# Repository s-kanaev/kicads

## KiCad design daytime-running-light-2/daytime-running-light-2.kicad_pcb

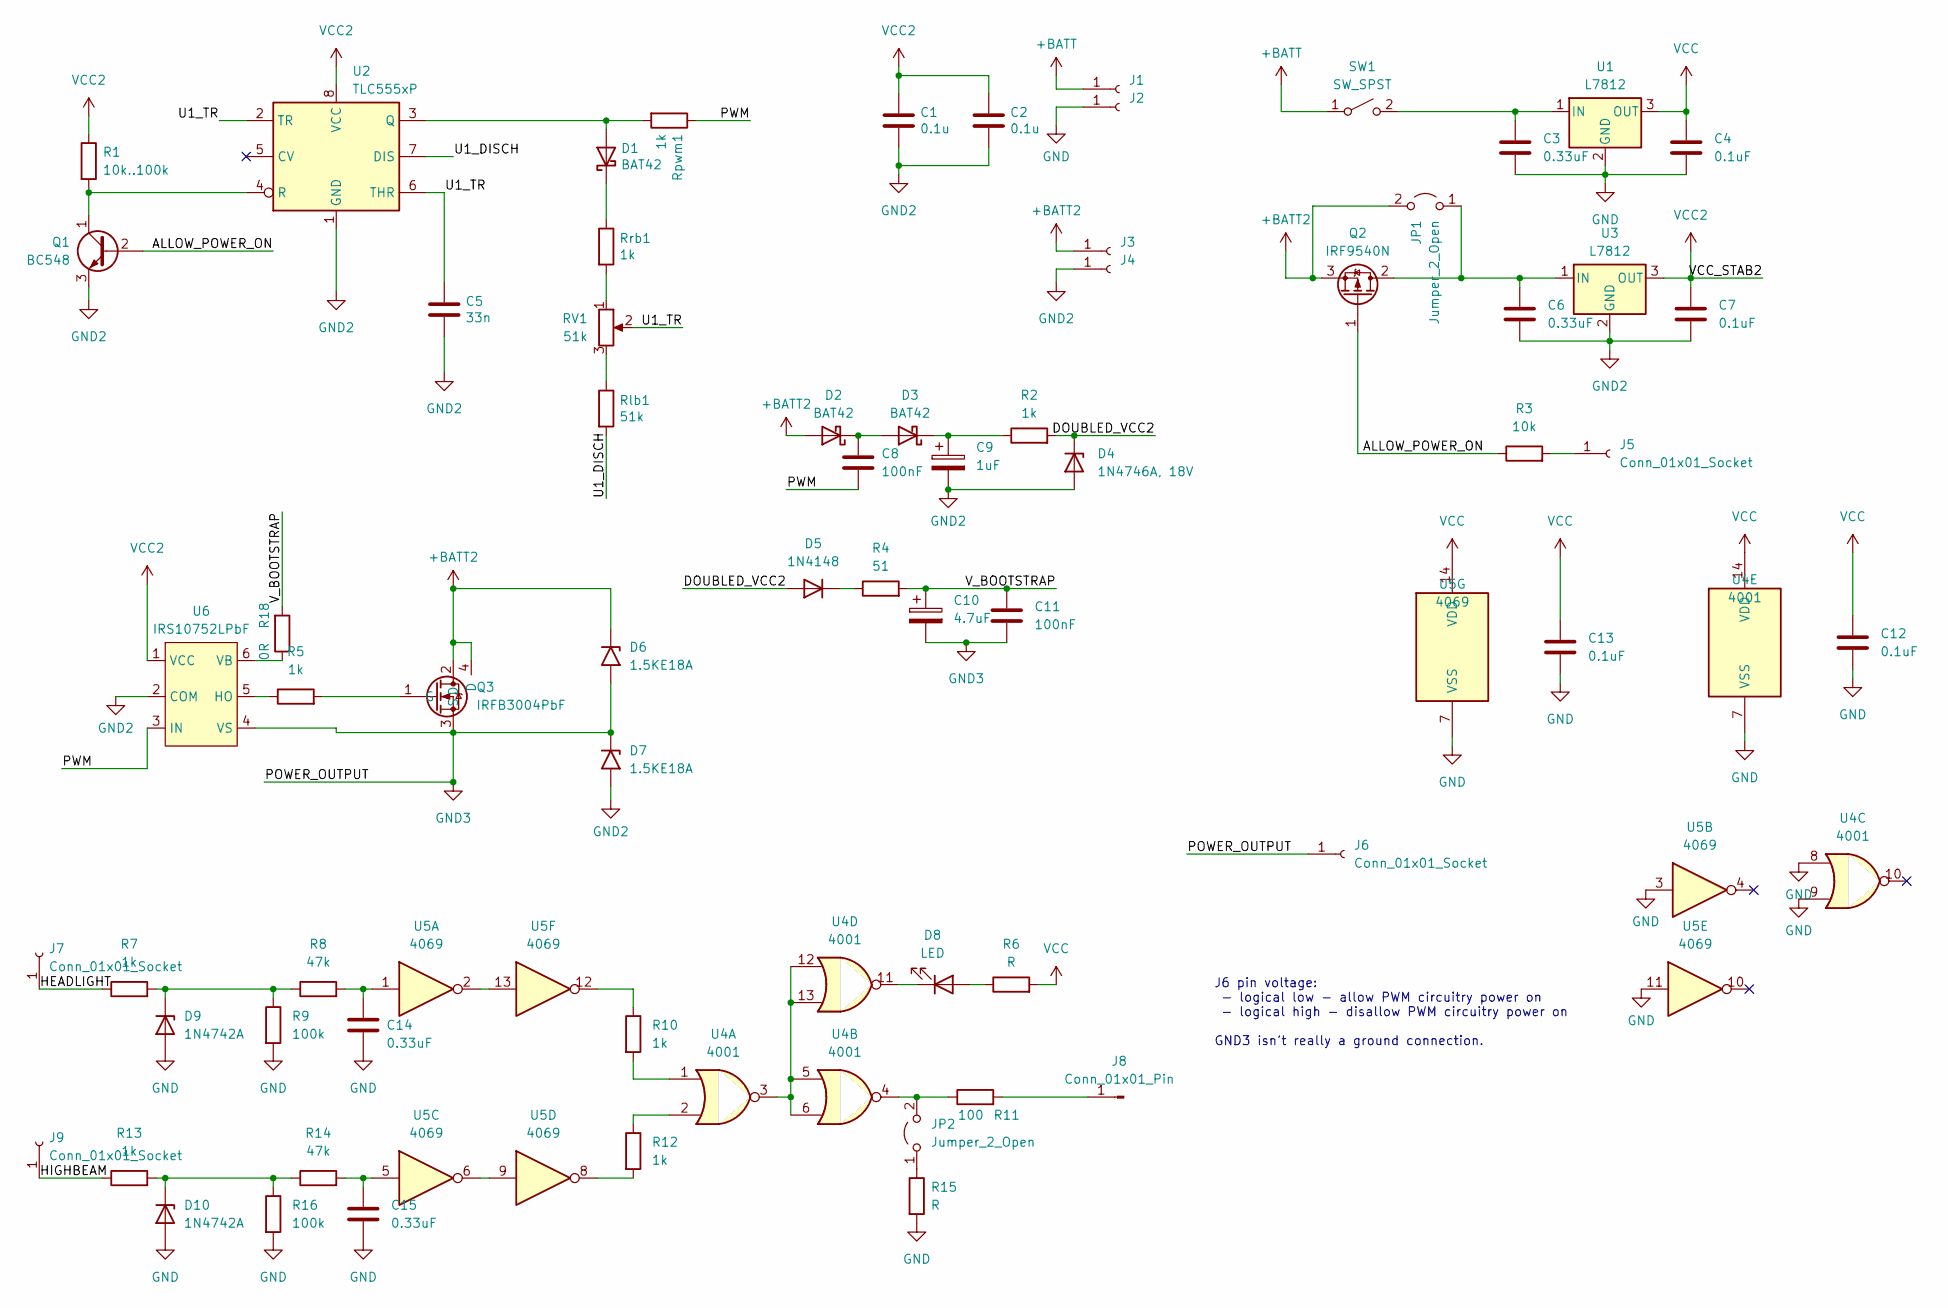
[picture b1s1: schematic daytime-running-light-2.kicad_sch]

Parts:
C1, C2: 0.1u; C_Disc_D6.0mm_W2.5mm_P5.00mm
C3, C6, C14, C15: 0.33uF; C_Disc_D6.0mm_W2.5mm_P5.00mm
C4, C7, C12, C13: 0.1uF; C_Disc_D6.0mm_W2.5mm_P5.00mm
C5: 33n; C_Disc_D6.0mm_W2.5mm_P5.00mm
C8, C11: 100nF; C_Disc_D6.0mm_W2.5mm_P5.00mm
C9: 1uF; CP_Radial_D5.0mm_P2.00mm
C10: 4.7uF; CP_Radial_D5.0mm_P2.00mm
D1: BAT42; D_DO-35_SOD27_P7.62mm_Horizontal
D2: BAT42; D_DO-35_SOD27_P5.08mm_Vertical_KathodeUp
D3: BAT42; D_DO-35_SOD27_P5.08mm_Vertical_AnodeUp
D4: 1N4746A, 18V; D_DO-41_SOD81_P3.81mm_Vertical_KathodeUp
D5: 1N4148; D_DO-35_SOD27_P7.62mm_Horizontal
D6, D7: 1.5KE18A; D_DO-201AE_P15.24mm_Horizontal
D8: LED; LED_D5.0mm
D9: 1N4742A; D_DO-41_SOD81_P3.81mm_Vertical_KathodeUp
D10: 1N4742A; D_DO-41_SOD81_P10.16mm_Horizontal
J1, J3, J6: Conn_01x01_Socket; SolderWire-2.5sqmm_1x01_D2.4mm_OD3.6mm
J2, J4: Conn_01x01_Socket; SolderWire-1.5sqmm_1x01_D1.7mm_OD3.9mm
J5, J7, J9: Conn_01x01_Socket; SolderWire-1.5sqmm_1x01_D1.7mm_OD3mm
J8: Conn_01x01_Pin; SolderWire-1.5sqmm_1x01_D1.7mm_OD3mm
JP1, JP2: Jumper_2_Open; SolderWire-0.75sqmm_1x02_P4.8mm_D1.25mm_OD2.3mm
Q1: BC548; TO-92_HandSolder2
Q2: IRF9540N; TO-220-3_Vertical-mod
Q3: IRFB3004PbF; TO-263-2
R1: 10k..100k; R_Axial_DIN0207_L6.3mm_D2.5mm_P7.62mm_Horizontal
R2, R7, R10, R12, R13: 1k; R_Axial_DIN0207_L6.3mm_D2.5mm_P2.54mm_Vertical
R3: 10k; R_Axial_DIN0207_L6.3mm_D2.5mm_P2.54mm_Vertical
R4: 51; R_Axial_DIN0207_L6.3mm_D2.5mm_P2.54mm_Vertical
R5: 1k; R_Axial_DIN0207_L6.3mm_D2.5mm_P7.62mm_Horizontal
R6, R15: R; R_Axial_DIN0207_L6.3mm_D2.5mm_P2.54mm_Vertical
R8, R14: 47k; R_Axial_DIN0207_L6.3mm_D2.5mm_P2.54mm_Vertical
R9, R16: 100k; R_Axial_DIN0207_L6.3mm_D2.5mm_P2.54mm_Vertical
R11: 100; R_Axial_DIN0207_L6.3mm_D2.5mm_P7.62mm_Horizontal
R18: 0R; R_Axial_DIN0207_L6.3mm_D2.5mm_P7.62mm_Horizontal
RV1: 51k; Potentiometer_Bourns_3296W_Vertical
Rlb1: 51k; R_Axial_DIN0207_L6.3mm_D2.5mm_P2.54mm_Vertical
Rpwm1: 1k; R_Axial_DIN0207_L6.3mm_D2.5mm_P5.08mm_Vertical
Rrb1: 1k; R_Axial_DIN0207_L6.3mm_D2.5mm_P7.62mm_Horizontal
SW1: SW_SPST; SolderWire-1.5sqmm_1x02_P6mm_D1.7mm_OD3mm
U1: L7812; TO-220-3_Vertical-mod
U2: TLC555xP; SOIC-8_3.9x4.9mm_P1.27mm
U3: L7812; TO-220-3_Vertical-mod2
U4: 4001; DIP-14_W7.62mm
U5: 4069; DIP-14_W7.62mm
U6: IRS10752LPbF; SOT-23-6_Handsoldering

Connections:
+BATT: J1.1, SW1.1 (A)
+BATT2: D2.2 (A), D6.1 (A1), J3.1, JP1.2 (B), Q2.3 (S), Q3.2 (D), Q3.4 (D)
/ALLOW_POWER_ON: Q1.2 (B), Q2.1 (G), R3.1
/DOUBLED_VCC2: D4.1 (K), D5.2 (A), R2.2
/HEADLIGHT: J7.1, R7.1
/HIGHBEAM: J9.1, R13.1
/PWM: C8.2, Rpwm1.1, U6.3 (IN)
/U1_DISCH: Rlb1.2, U2.7 (DIS)
/U1_TR: C5.1, RV1.2, U2.2 (TR), U2.6 (THR)
/V_BOOTSTRAP: C10.1, C11.1, R4.2, R18.2
GND: C3.2, C4.2, C12.2, C13.2, C14.2, C15.2, D9.2 (A), D10.2 (A), J2.1, R9.2, R15.2, R16.2, U1.2 (GND), U4.7 (VSS), U4.8, U4.9, U5.3, U5.7 (VSS), U5.11
GND2: C1.2, C2.2, C5.2, C6.2, C7.2, C9.2, D4.2 (A), D7.2 (A2), J4.1, Q1.3 (E), U2.1 (GND), U3.2 (GND), U6.2 (COM)
GND3: C10.2, C11.2, D6.2 (A2), D7.1 (A1), J6.1, Q3.3 (S), U6.4 (VS)
unnamed: C14.1, R8.2, U5.1
unnamed: C15.1, R14.2, U5.5
unnamed: D1.2 (A), Rpwm1.2, U2.3 (Q)
unnamed: D1.1 (K), Rrb1.1
unnamed: C8.1, D2.1 (K), D3.2 (A)
unnamed: C9.1, D3.1 (K), R2.1
unnamed: D5.1 (K), R4.1
unnamed: D8.2 (A), R6.1
unnamed: D8.1 (K), U4.11
unnamed: D9.1 (K), R7.2, R8.1, R9.1
unnamed: D10.1 (K), R13.2, R14.1, R16.1
unnamed: J5.1, R3.2
unnamed: J8.1, R11.2
unnamed: C6.1, JP1.1 (A), Q2.2 (D), U3.1 (IN)
unnamed: JP2.1 (A), R15.1
unnamed: JP2.2 (B), R11.1, U4.4
unnamed: Q1.1 (C), R1.2, U2.4 (R)
unnamed: Q3.1 (G), R5.2
unnamed: R10.1, U5.12
unnamed: R10.2, U4.1
unnamed: R12.1, U4.2
unnamed: R12.2, U5.8
unnamed: RV1.1, Rrb1.2
unnamed: RV1.3, Rlb1.1
unnamed: C3.1, SW1.2 (B), U1.1 (IN)
unnamed: U4.3, U4.5, U4.6, U4.12, U4.13
unnamed: U5.6, U5.9
unnamed: U5.2, U5.13
unnamed: R5.1, U6.5 (HO)
unnamed: R18.1, U6.6 (VB)
VCC: C4.1, C12.1, C13.1, R6.2, U1.3 (OUT), U4.14 (VDD), U5.14 (VDD)
VCC2: C1.1, C2.1, C7.1, R1.1, U2.8 (VCC), U3.3 (OUT), U6.1 (VCC)

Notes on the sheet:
J6 pin voltage: - logical low - allow PWM circuitry power on - logical high - disallow PWM circuitry power on GND3 isn't really a ground connection.

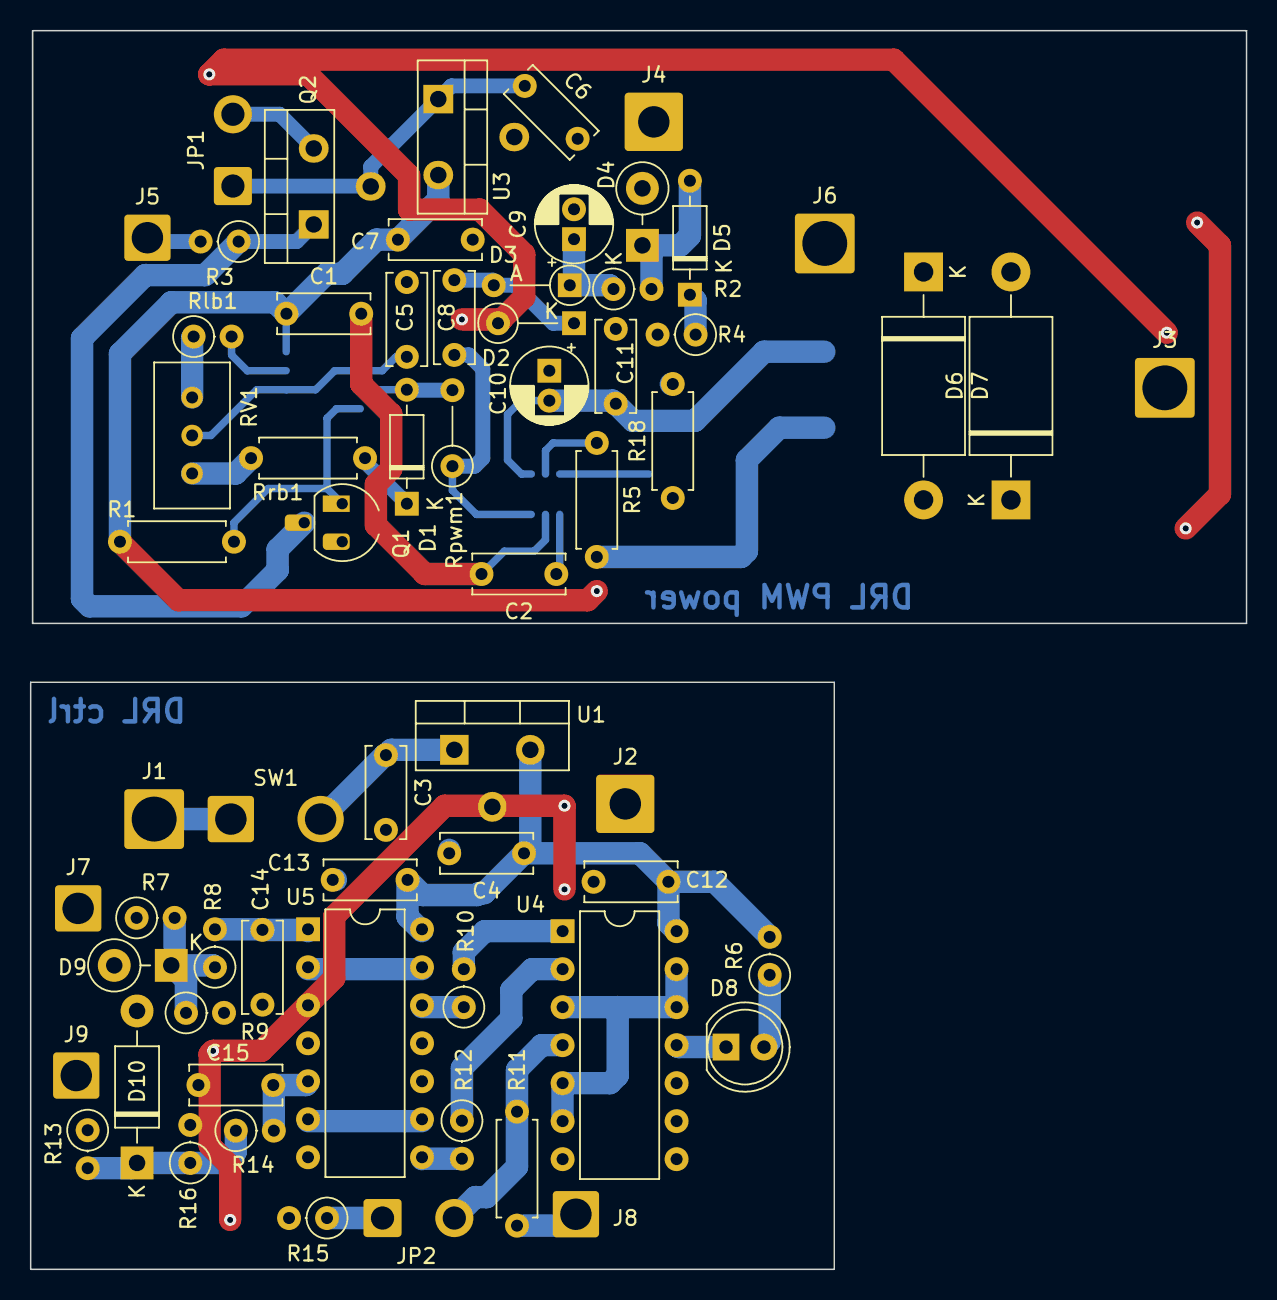
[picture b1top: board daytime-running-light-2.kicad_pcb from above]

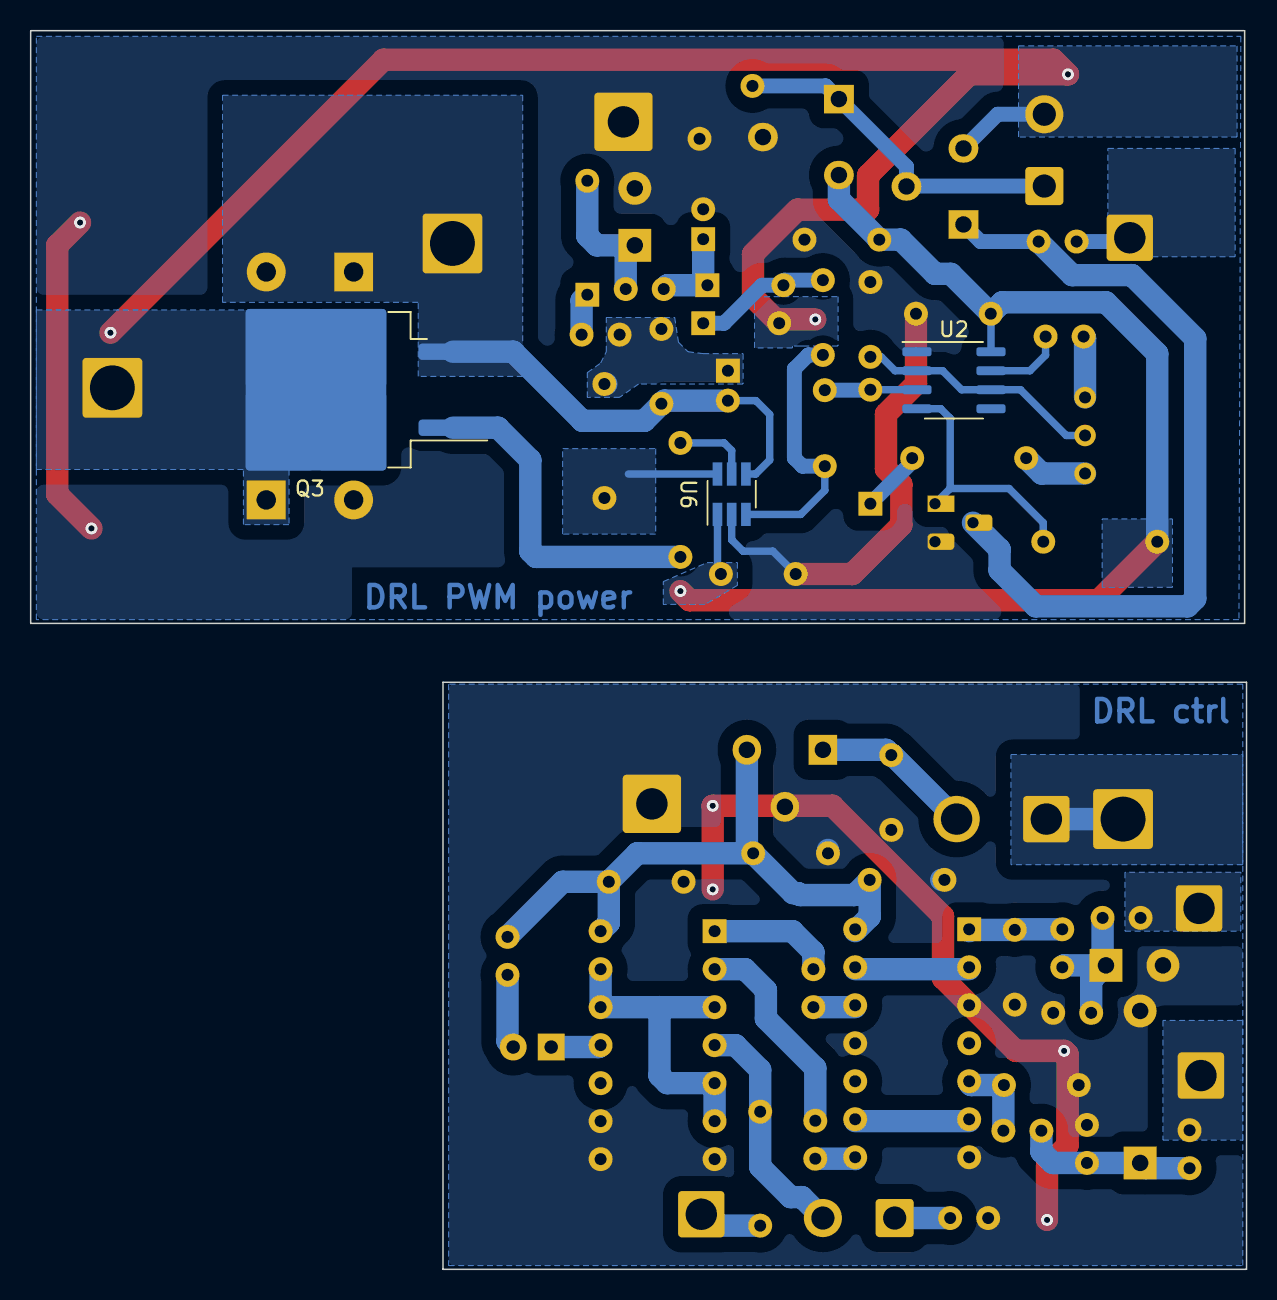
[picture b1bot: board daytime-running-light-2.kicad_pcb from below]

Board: 2 copper layers, 81.3 x 82.8 mm, 67 parts (3 on the bottom side), 45 nets.

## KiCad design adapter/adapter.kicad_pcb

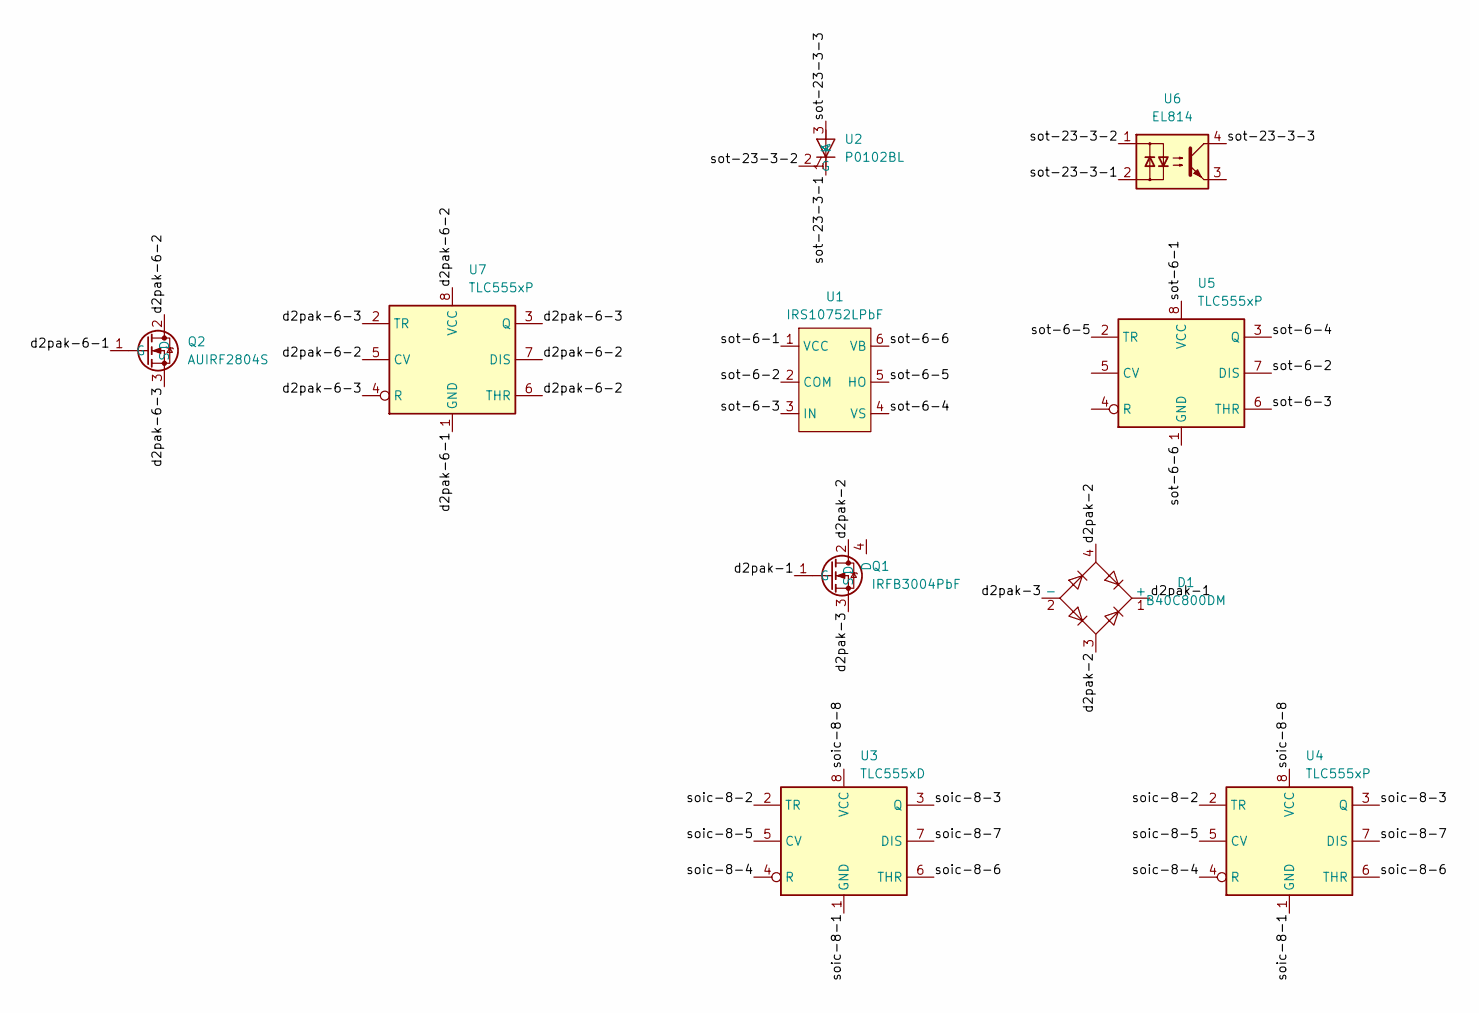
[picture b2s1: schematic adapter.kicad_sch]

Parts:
D1: B40C800DM; Diode_Bridge_DIP-4_W7.62mm_P5.08mm
Q1: IRFB3004PbF; TO-263-2
Q2: AUIRF2804S; AUIRF2804S TO-263-6
U1: IRS10752LPbF; SOT-23-6_Handsoldering
U2: P0102BL; SOT-23-3
U3: TLC555xD; SOIC-8_3.9x4.9mm_P1.27mm
U4: TLC555xP; DIP-8_W10.16mm
U5, U7: TLC555xP; DIP-8_W7.62mm
U6: EL814; DIP-4_W7.62mm_LongPads

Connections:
/d2pak-1: D1.1 (+), Q1.1 (G)
/d2pak-2: D1.3, D1.4, Q1.2 (D)
/d2pak-3: D1.2 (-), Q1.3 (S)
/d2pak-6-1: Q2.1 (G), U7.1 (GND)
/d2pak-6-2: Q2.2 (D), U7.5 (CV), U7.6 (THR), U7.7 (DIS), U7.8 (VCC)
/d2pak-6-3: Q2.3 (S), U7.2 (TR), U7.3 (Q), U7.4 (R)
/soic-8-1: U3.1 (GND), U4.1 (GND)
/soic-8-2: U3.2 (TR), U4.2 (TR)
/soic-8-3: U3.3 (Q), U4.3 (Q)
/soic-8-4: U3.4 (R), U4.4 (R)
/soic-8-5: U3.5 (CV), U4.5 (CV)
/soic-8-6: U3.6 (THR), U4.6 (THR)
/soic-8-7: U3.7 (DIS), U4.7 (DIS)
/soic-8-8: U3.8 (VCC), U4.8 (VCC)
/sot-6-1: U1.1 (VCC), U5.8 (VCC)
/sot-6-2: U1.2 (COM), U5.7 (DIS)
/sot-6-3: U1.3 (IN), U5.6 (THR)
/sot-6-4: U1.4 (VS), U5.3 (Q)
/sot-6-5: U1.5 (HO), U5.2 (TR)
/sot-6-6: U1.6 (VB), U5.1 (GND)
/sot-23-3-1: U2.1 (K), U6.2
/sot-23-3-2: U2.2 (G), U6.1
/sot-23-3-3: U2.3 (A), U6.4

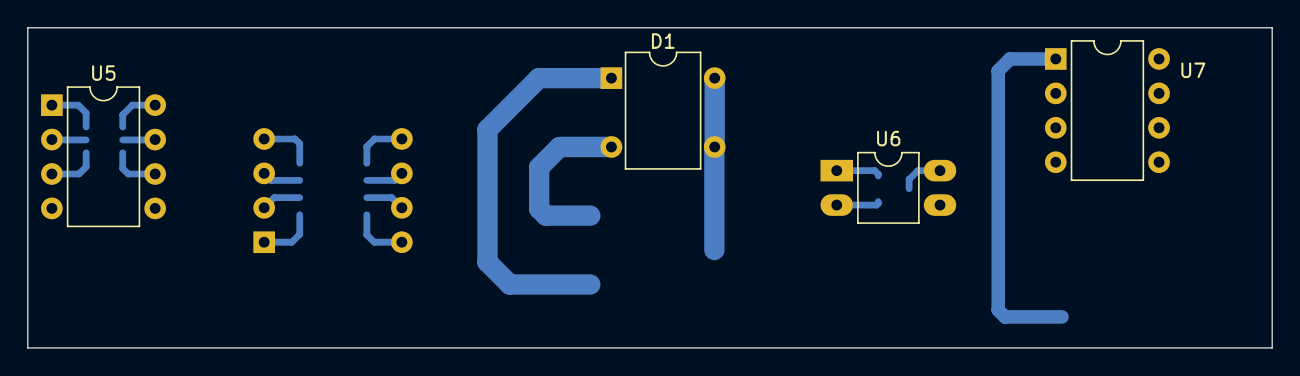
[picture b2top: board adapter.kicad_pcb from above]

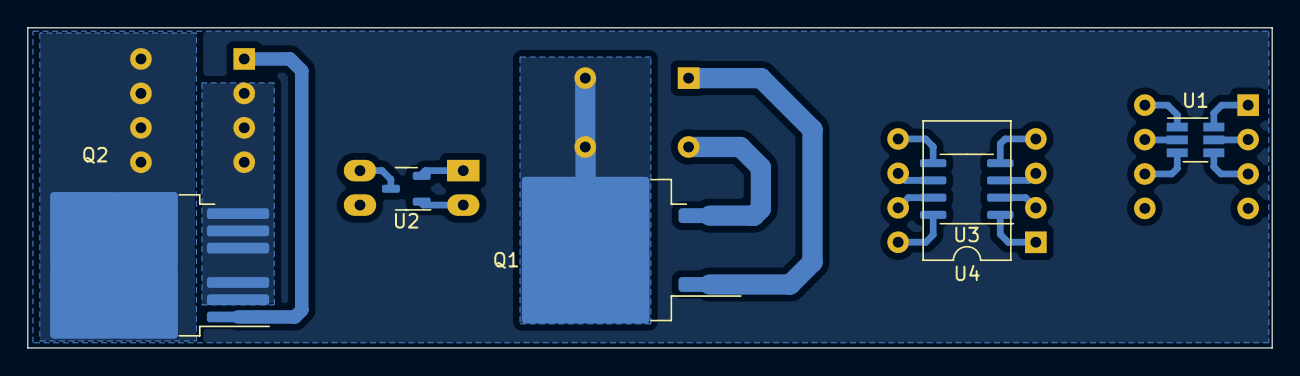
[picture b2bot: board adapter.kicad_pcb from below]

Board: 2 copper layers, 91.8 x 23.6 mm, 10 parts (6 on the bottom side), 23 nets.

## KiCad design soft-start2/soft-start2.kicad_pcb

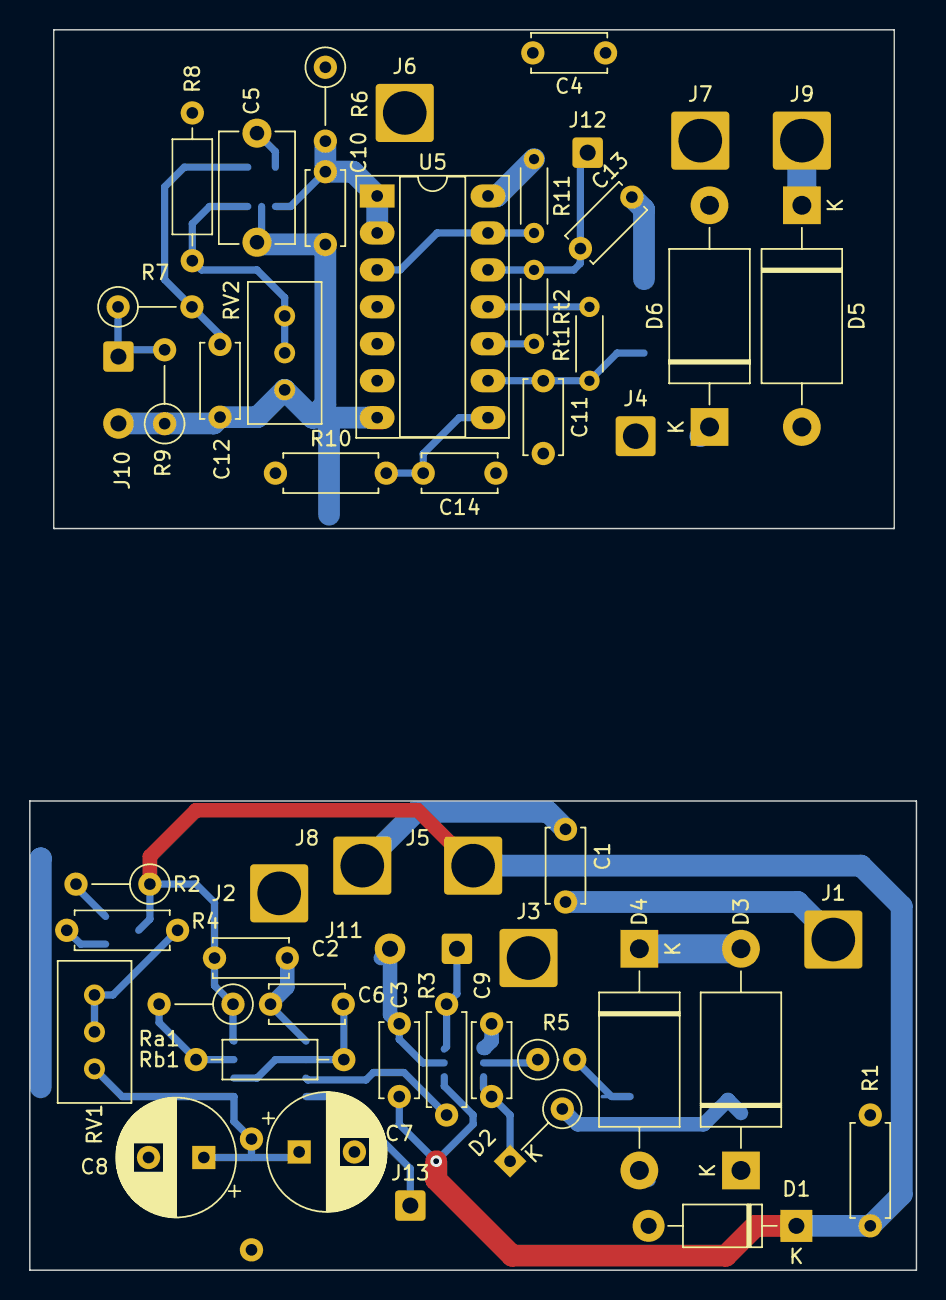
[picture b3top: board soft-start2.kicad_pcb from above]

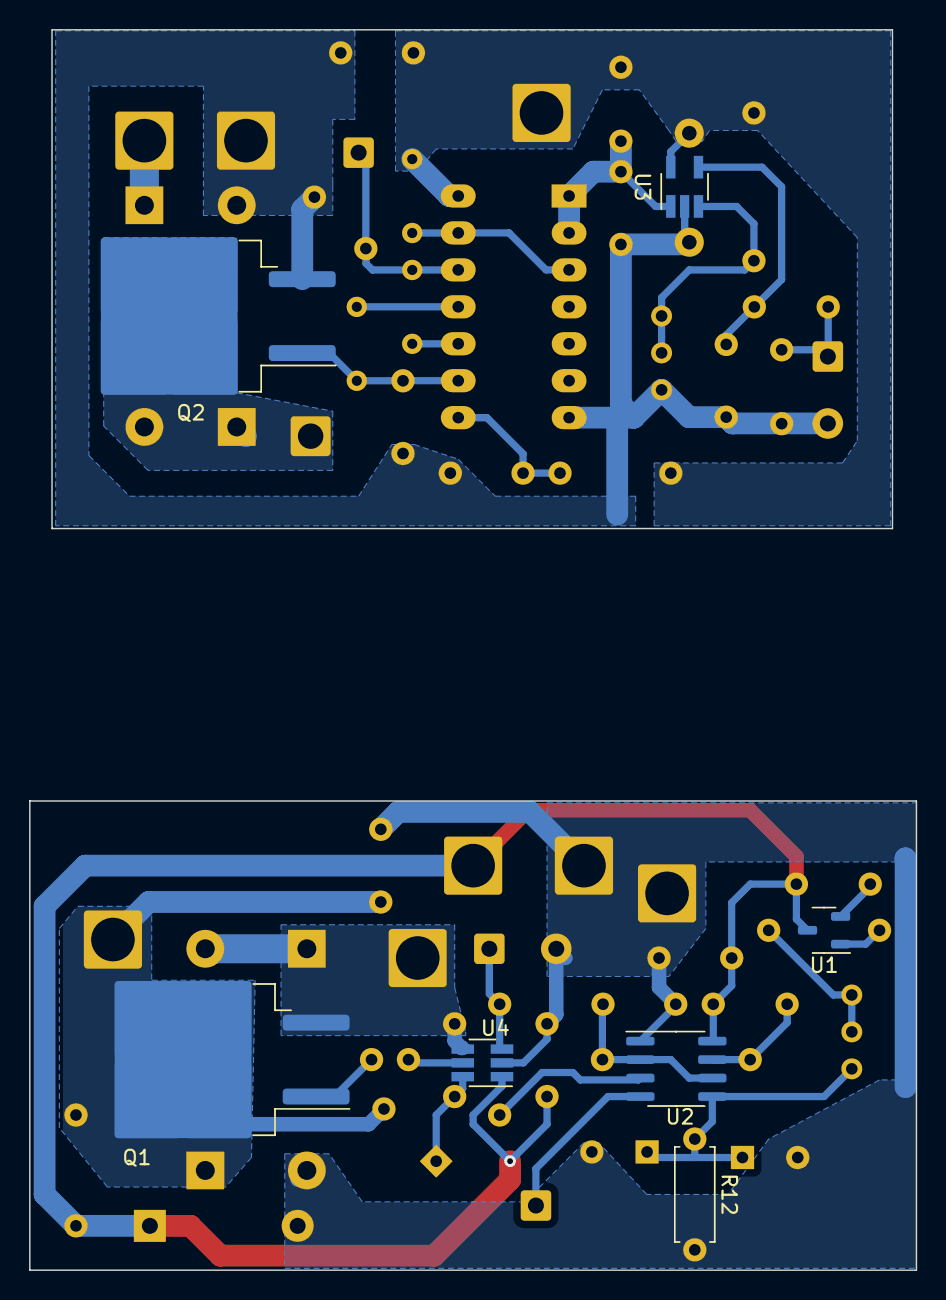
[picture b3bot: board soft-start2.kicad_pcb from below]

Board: 2 copper layers, 61.0 x 85.3 mm, 58 parts (7 on the bottom side), 30 nets.

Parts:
C1, C2, C3, C4, C9: C; C_Disc_D5.0mm_W2.5mm_P5.00mm
C5: C; C_Disc_D7.5mm_W5.0mm_P7.50mm
C6: 0.1uF; C_Disc_D5.0mm_W2.5mm_P5.00mm
C7, C8: 470uF; CP_Radial_D8.0mm_P3.80mm
C10, C11, C13, C14: 22nF; C_Disc_D5.0mm_W2.5mm_P5.00mm
C12: 0.22uF; C_Disc_D5.0mm_W2.5mm_P5.00mm
D1: 1N4740A; D_DO-41_SOD81_P10.16mm_Horizontal
D2: 1N4148; D_DO-35_SOD27_P5.08mm_Vertical_KathodeUp
D3, D4, D5, D6: 1.5KExxA; D_DO-201AE_P15.24mm_Horizontal
J1, J2, J6, J7, J9: SolderWire-2.5sqmm_1x01_D2.4mm_OD3.6mm
J3, J5, J8: Conn_01x01_Pin; SolderWire-2.5sqmm_1x01_D2.4mm_OD3.6mm
J4: Conn_01x01_Pin; SolderWire-1sqmm_1x01_D1.4mm_OD2.7mm
J10: Conn_01x02_Pin; SolderWire-0.5sqmm_1x02_P4.6mm_D0.9mm_OD2.1mm
J11: Conn_01x02_Socket; SolderWire-0.5sqmm_1x02_P4.6mm_D0.9mm_OD2.1mm
J12: Conn_01x01_Pin; SolderWire-0.5sqmm_1x01_D0.9mm_OD2.1mm
J13: Conn_01x01_Socket; SolderWire-0.5sqmm_1x01_D0.9mm_OD2.1mm
Q1, Q2: IRFB3004PbF; TO-263-2
R1: 150, 0.25W; R_Axial_DIN0207_L6.3mm_D2.5mm_P7.62mm_Horizontal
R2: R; R_Axial_DIN0207_L6.3mm_D2.5mm_P5.08mm_Vertical
R3: 1k; R_Axial_DIN0207_L6.3mm_D2.5mm_P7.62mm_Horizontal
R4: 200; R_Axial_DIN0207_L6.3mm_D2.5mm_P7.62mm_Horizontal
R5: 1k; R_Axial_DIN0207_L6.3mm_D2.5mm_P2.54mm_Vertical
R6: 5.1k; R_Axial_DIN0207_L6.3mm_D2.5mm_P5.08mm_Vertical
R7: 160k; R_Axial_DIN0207_L6.3mm_D2.5mm_P5.08mm_Vertical
R8: 220k; R_Axial_DIN0207_L6.3mm_D2.5mm_P10.16mm_Horizontal
R9: 100k; R_Axial_DIN0207_L6.3mm_D2.5mm_P5.08mm_Vertical
R10: 5.1k; R_Axial_DIN0207_L6.3mm_D2.5mm_P7.62mm_Horizontal
R11: 5.1k; R_Axial_DIN0204_L3.6mm_D1.6mm_P5.08mm_Horizontal
R12: 24k; R_Axial_DIN0207_L6.3mm_D2.5mm_P7.62mm_Horizontal
RV1: 2.2k; Potentiometer_Bourns_3296W_Vertical
RV2: 1M; Potentiometer_Bourns_3296W_Vertical
Ra1: 10k; R_Axial_DIN0207_L6.3mm_D2.5mm_P5.08mm_Vertical
Rb1: 1k; R_Axial_DIN0207_L6.3mm_D2.5mm_P10.16mm_Horizontal
Rt1, Rt2: 5.1k; R_Axial_DIN0204_L3.6mm_D1.6mm_P5.08mm_Horizontal
U1: P0102BL; SOT-23-3
U2: TLC555xD; SOIC-8_3.9x4.9mm_P1.27mm
U3: TS391ILT; SOT-23-5_HandSoldering
U4: IRS10752LPbF; SOT-23-6_Handsoldering
U5: 4011; DIP-14_W7.62mm_Socket_LongPads

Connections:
+BATT: C1.1, D2.2 (A), D3.1 (A1), J1.1, Q1.2 (D), R1.1
+BATT2: D5.1 (A1), J9.1
/INT: C12.1, R7.2, U3.4 (+)
/INT_REF: R8.2, RV2.1, RV2.2, U3.3 (-)
/POWER_OUTPUT: C9.2, D3.2 (A2), D4.1 (A1), J3.1, Q1.3 (S), U4.4 (VS)
/PWM: J11.1, R3.2, U4.3 (IN)
/PWM2: J10.1, R7.1, R9.2
/TRIGGER_OUT: C11.1, Q2.1 (G), Rt1.1, U5.9
/TRIGGER_OUT_INV: C13.1, J12.1, Rt2.1, U5.12
/TRIGGER_RESET: C14.1, R10.2, U5.8
/TRIGGER_SET: R11.2, U5.3, U5.13
/U1_CONT: C7.1, C8.1, R12.1, RV1.3, U2.5 (CV)
/U1_DISCH: Ra1.2, Rb1.1, U2.7 (DIS)
/U1_TRIG: C6.1, Rb1.2, U2.2 (TR), U2.6 (THR)
GND: C1.2, C2.2, C3.2, C6.2, C7.2, C8.2, D1.2 (A), D4.2 (A2), J2.1, J8.1, J11.2, R12.2, U2.1 (GND), U4.2 (COM)
GND2: C4.2, C5.2, C10.2, C11.2, C12.2, C13.2, C14.2, D6.2 (A2), J7.1, J10.2, Q2.3 (S), R9.1, RV2.3, U3.2 (VCC-), U5.7 (VSS)
unnamed: C10.1, R6.2, U3.1, U5.1, U5.2
unnamed: C9.1, D2.1 (K), U4.6 (VB)
unnamed: D5.2 (A2), D6.1 (A1), J4.1, Q2.2 (D)
unnamed: J13.1, U2.4 (R)
unnamed: Q1.1 (G), R5.2
unnamed: R4.2, RV1.1, RV1.2
unnamed: Rt1.2, U5.11
unnamed: Rt2.2, U5.10
unnamed: R2.2, U1.2 (G)
unnamed: R4.1, U1.1 (K)
unnamed: R3.1, U2.3 (Q)
unnamed: R5.1, U4.5 (HO)
VCC: C2.1, C3.1, D1.1 (K), J5.1, R1.2, R2.1, Ra1.1, U1.3 (A), U2.8 (VCC), U4.1 (VCC)
VCC2: C4.1, C5.1, J6.1, R6.1, R8.1, R10.1, R11.1, U3.5 (VCC+), U5.14 (VDD)

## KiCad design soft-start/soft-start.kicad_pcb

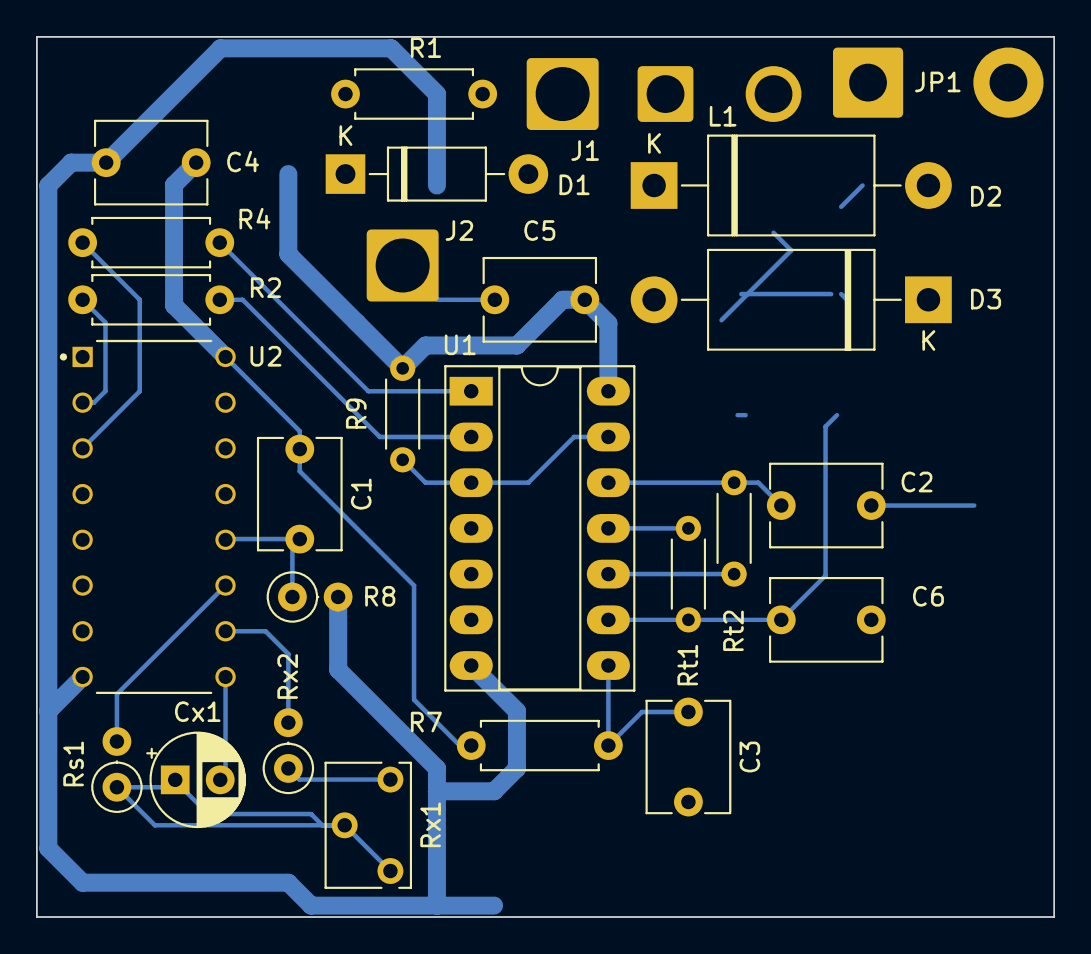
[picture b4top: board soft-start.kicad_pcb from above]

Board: 2 copper layers, 56.5 x 48.9 mm, 28 parts (1 on the bottom side), 20 nets.

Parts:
C1, C2, C3, C6: 22nF; C_Disc_D6.0mm_W4.4mm_P5.00mm
C4, C5: 0.1u; C_Disc_D6.0mm_W4.4mm_P5.00mm
Cx1: 11nF; CP_Radial_D5.0mm_P2.50mm
D1: 1N4740A; D_DO-41_SOD81_P10.16mm_Horizontal
D2, D3: 1.5KExxA; D_DO-201AE_P15.24mm_Horizontal
J1, J2: SolderWire-2.5sqmm_1x01_D2.4mm_OD3.6mm
JP1: Jumper_2_Open; SolderWire-1.5sqmm_1x02_P7.8mm_D1.7mm_OD3.9mm
L1: 12V Relay; SolderWire-1.5sqmm_1x02_P6mm_D1.7mm_OD3mm
Q1: IRFB3004PbF; TO-263-2
R1: 150, 0.25W; R_Axial_DIN0207_L6.3mm_D2.5mm_P7.62mm_Horizontal
R2, R4: 51k; R_Axial_DIN0207_L6.3mm_D2.5mm_P7.62mm_Horizontal
R7: 5.1k; R_Axial_DIN0207_L6.3mm_D2.5mm_P7.62mm_Horizontal
R8: 5.1k; R_Axial_DIN0207_L6.3mm_D2.5mm_P2.54mm_Vertical
R9: 5.1k; R_Axial_DIN0204_L3.6mm_D1.6mm_P5.08mm_Horizontal
Rs1: (2..10) * Rx; R_Axial_DIN0207_L6.3mm_D2.5mm_P2.54mm_Vertical
Rt1, Rt2: 5.1k; R_Axial_DIN0204_L3.6mm_D1.6mm_P5.08mm_Horizontal
Rx1: 5k; Potentiometer_Bourns_3266W_Vertical
Rx2: 4.7k; R_Axial_DIN0207_L6.3mm_D2.5mm_P2.54mm_Vertical
U1: 4011; DIP-14_W7.62mm_Socket_LongPads
U2: CD4060BE; DIP794W45P254L1969H508Q16

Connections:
+BATT: D2.1 (A1), J1.1, L1.1 (-), R1.1
/COUNTER_RESET: C1.2, R8.1, U2.12 (RESET)
/TRIGGER_OUT: C6.1, Q1.1 (G), Rt1.1, U1.9
/TRIGGER_RESET: C3.1, R7.2, U1.8
/TRIGGER_SET: R9.2, U1.3, U1.13
GND: C2.2, C3.2, C4.2, C5.2, C6.2, D1.2 (A), D3.2 (A2), J2.1, JP1.2 (B), Q1.3 (S), R8.2, U1.7 (VSS), U2.8 (VSS)
unnamed: C2.1, Rt2.1, U1.12
unnamed: Cx1.1, Rs1.1, Rx1.1, Rx1.2
unnamed: D2.2 (A2), D3.1 (A1), JP1.1 (A), L1.2 (+), Q1.2 (D)
unnamed: R2.2, U1.2
unnamed: R4.2, U1.1
unnamed: Rt1.2, U1.11
unnamed: Rt2.2, U1.10
unnamed: Rx1.3, Rx2.1
unnamed: Rs1.2, U2.11 ((PHI)I)
unnamed: Cx1.2, U2.9 ((PHI)O)
unnamed: R2.1, U2.2 (Q13)
unnamed: R4.1, U2.3 (Q14)
unnamed: Rx2.2, U2.10 (~(PHI)O~)
VCC: C1.1, C4.1, C5.1, D1.1 (K), R1.2, R7.1, R9.1, U1.14 (VDD), U2.16 (VDD)

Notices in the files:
parts and their libraries:
Copyright 2021 Accelerated Designs. All rights reserved.
